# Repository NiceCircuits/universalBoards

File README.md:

# universalBoards
Universal boards for SMD and other. Quick and dirty, 50x50mm - to make in Seeed Studio.

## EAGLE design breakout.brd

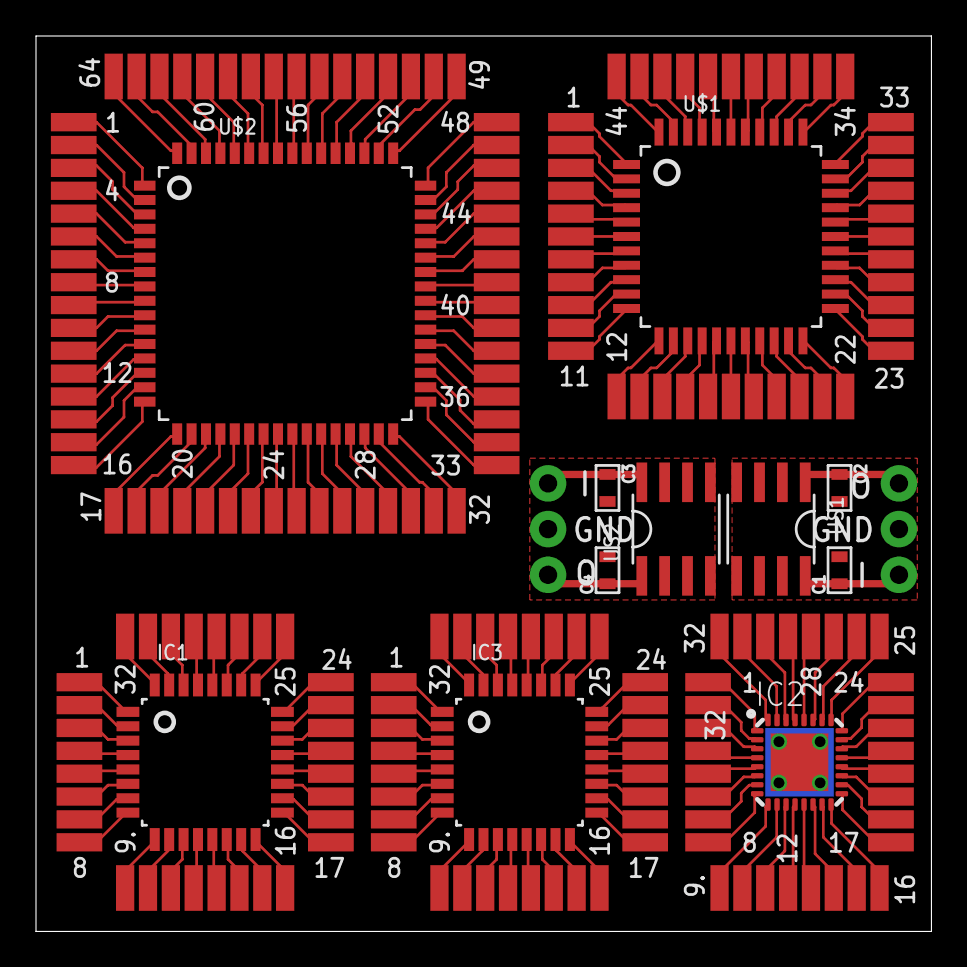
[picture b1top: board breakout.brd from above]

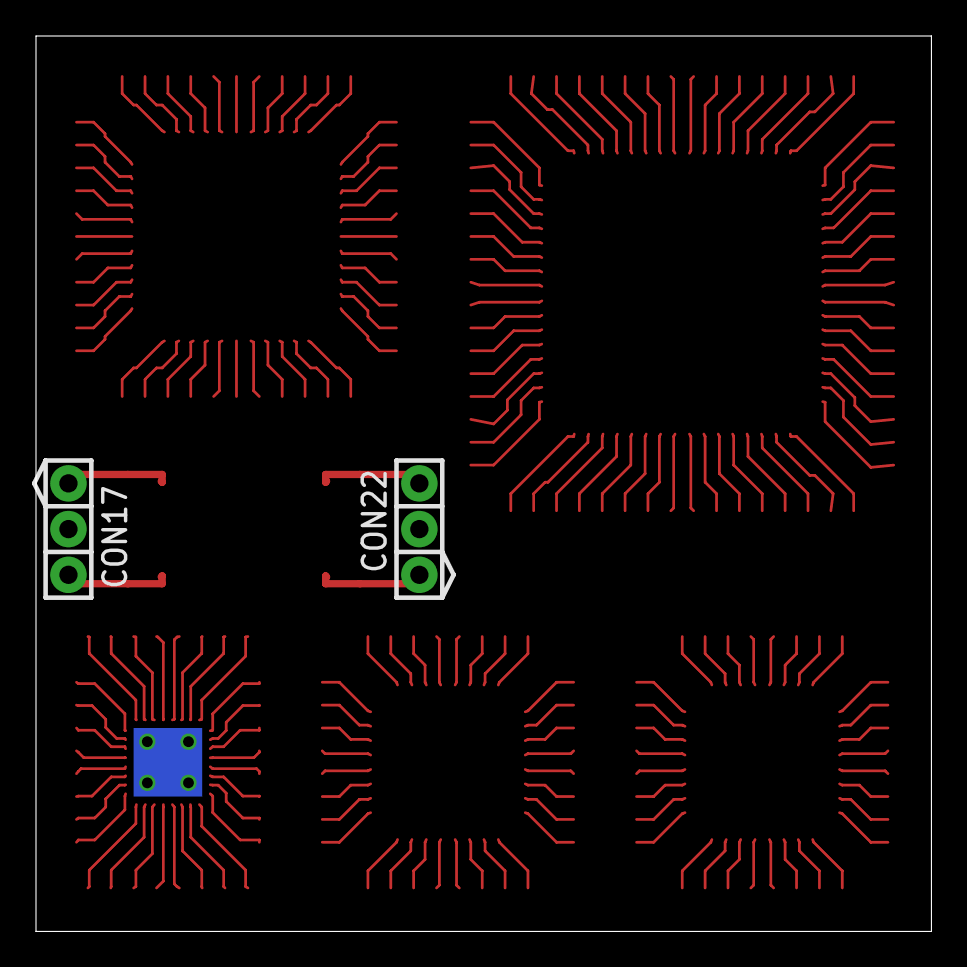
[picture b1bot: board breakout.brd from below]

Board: 2 copper layers, 49.7 x 49.7 mm, 33 parts (2 on the bottom side), 210 nets.

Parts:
C1, C2, C3, C4: 0603
CON1, CON2, CON3, CON4, CON13, CON14, CON15, CON16, CON18, CON19, CON20, CON21: PIN8X1_SM50
CON5, CON6, CON7, CON8: PIN11X1_SM50
CON9, CON10, CON11, CON12: PIN16X1_SM50
CON17, CON22: PIN3X1
IC1, IC3: TQFP32
IC2: MLF32-TH
U$1: 44TQFP; TQFP44
U$2: 64TQFP; TQFP64
US1, US2: SO08

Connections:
unnamed: CON1.P$1, IC1.1
unnamed: CON1.P$2, IC1.2
unnamed: CON1.P$3, IC1.3
unnamed: CON1.P$4, IC1.4
unnamed: CON1.P$5, IC1.5
unnamed: CON1.P$6, IC1.6
unnamed: CON1.P$7, IC1.7
unnamed: CON1.P$8, IC1.8
unnamed: CON2.P$1, IC1.9
unnamed: CON2.P$2, IC1.10
unnamed: CON2.P$3, IC1.11
unnamed: CON2.P$4, IC1.12
unnamed: CON2.P$5, IC1.13
unnamed: CON2.P$6, IC1.14
unnamed: CON2.P$7, IC1.15
unnamed: CON2.P$8, IC1.16
unnamed: CON3.P$1, IC1.17
unnamed: CON3.P$2, IC1.18
unnamed: CON3.P$3, IC1.19
unnamed: CON3.P$4, IC1.20
unnamed: CON3.P$5, IC1.21
unnamed: CON3.P$6, IC1.22
unnamed: CON3.P$7, IC1.23
unnamed: CON3.P$8, IC1.24
unnamed: CON4.P$1, IC1.25
unnamed: CON4.P$2, IC1.26
unnamed: CON4.P$3, IC1.27
unnamed: CON4.P$4, IC1.28
unnamed: CON4.P$5, IC1.29
unnamed: CON4.P$6, IC1.30
unnamed: CON4.P$7, IC1.31
unnamed: CON4.P$8, IC1.32
unnamed: CON5.P$1, U$1.1
unnamed: CON5.P$2, U$1.2
unnamed: CON5.P$3, U$1.3
unnamed: CON5.P$4, U$1.4
unnamed: CON5.P$5, U$1.5
unnamed: CON5.P$6, U$1.6
unnamed: CON5.P$7, U$1.7
unnamed: CON5.P$8, U$1.8
unnamed: CON5.P$9, U$1.9
unnamed: CON5.P$10, U$1.10
unnamed: CON5.P$11, U$1.11
unnamed: CON6.P$1, U$1.12
unnamed: CON6.P$2, U$1.13
unnamed: CON6.P$3, U$1.14
unnamed: CON6.P$4, U$1.15
unnamed: CON6.P$5, U$1.16
unnamed: CON6.P$6, U$1.17
unnamed: CON6.P$7, U$1.18
unnamed: CON6.P$8, U$1.19
unnamed: CON6.P$9, U$1.20
unnamed: CON6.P$10, U$1.21
unnamed: CON6.P$11, U$1.22
unnamed: CON7.P$1, U$1.23
unnamed: CON7.P$2, U$1.24
unnamed: CON7.P$3, U$1.25
unnamed: CON7.P$4, U$1.26
unnamed: CON7.P$5, U$1.27
unnamed: CON7.P$6, U$1.28
unnamed: CON7.P$7, U$1.29
unnamed: CON7.P$8, U$1.30
unnamed: CON7.P$9, U$1.31
unnamed: CON7.P$10, U$1.32
unnamed: CON7.P$11, U$1.33
unnamed: CON8.P$1, U$1.34
unnamed: CON8.P$2, U$1.35
unnamed: CON8.P$3, U$1.36
unnamed: CON8.P$4, U$1.37
unnamed: CON8.P$5, U$1.38
unnamed: CON8.P$6, U$1.39
unnamed: CON8.P$7, U$1.40
unnamed: CON8.P$8, U$1.41
unnamed: CON8.P$9, U$1.42
unnamed: CON8.P$10, U$1.43
unnamed: CON8.P$11, U$1.44
unnamed: CON9.P$1, U$2.1
unnamed: CON9.P$2, U$2.2
unnamed: CON9.P$3, U$2.3
unnamed: CON9.P$4, U$2.4
unnamed: CON9.P$5, U$2.5
unnamed: CON9.P$6, U$2.6
unnamed: CON9.P$7, U$2.7
unnamed: CON9.P$8, U$2.8
unnamed: CON9.P$9, U$2.9
unnamed: CON9.P$10, U$2.10
unnamed: CON9.P$11, U$2.11
unnamed: CON9.P$12, U$2.12
unnamed: CON9.P$13, U$2.13
unnamed: CON9.P$14, U$2.14
unnamed: CON9.P$15, U$2.15
unnamed: CON9.P$16, U$2.16
unnamed: CON10.P$1, U$2.17
unnamed: CON10.P$2, U$2.18
unnamed: CON10.P$3, U$2.19
unnamed: CON10.P$4, U$2.20
unnamed: CON10.P$5, U$2.21
unnamed: CON10.P$6, U$2.22
unnamed: CON10.P$7, U$2.23
unnamed: CON10.P$8, U$2.24
unnamed: CON10.P$9, U$2.25
unnamed: CON10.P$10, U$2.26
unnamed: CON10.P$11, U$2.27
unnamed: CON10.P$12, U$2.28
unnamed: CON10.P$13, U$2.29
unnamed: CON10.P$14, U$2.30
unnamed: CON10.P$15, U$2.31
unnamed: CON10.P$16, U$2.32
unnamed: CON11.P$1, U$2.33
unnamed: CON11.P$2, U$2.34
unnamed: CON11.P$3, U$2.35
unnamed: CON11.P$4, U$2.36
unnamed: CON11.P$5, U$2.37
unnamed: CON11.P$6, U$2.38
unnamed: CON11.P$7, U$2.39
unnamed: CON11.P$8, U$2.40
unnamed: CON11.P$9, U$2.41
unnamed: CON11.P$10, U$2.42
unnamed: CON11.P$11, U$2.43
unnamed: CON11.P$12, U$2.44
unnamed: CON11.P$13, U$2.45
unnamed: CON11.P$14, U$2.46
unnamed: CON11.P$15, U$2.47
unnamed: CON11.P$16, U$2.48
unnamed: CON12.P$1, U$2.49
unnamed: CON12.P$2, U$2.50
unnamed: CON12.P$3, U$2.51
unnamed: CON12.P$4, U$2.52
unnamed: CON12.P$5, U$2.53
unnamed: CON12.P$6, U$2.54
unnamed: CON12.P$7, U$2.55
unnamed: CON12.P$8, U$2.56
unnamed: CON12.P$9, U$2.57
unnamed: CON12.P$10, U$2.58
unnamed: CON12.P$11, U$2.59
unnamed: CON12.P$12, U$2.60
unnamed: CON12.P$13, U$2.61
unnamed: CON12.P$14, U$2.62
unnamed: CON12.P$15, U$2.63
unnamed: CON12.P$16, U$2.64
unnamed: CON13.P$1, IC2.1
unnamed: CON13.P$2, IC2.2
unnamed: CON13.P$3, IC2.3
unnamed: CON13.P$4, IC2.4
unnamed: CON13.P$5, IC2.5
unnamed: CON13.P$6, IC2.6
unnamed: CON13.P$7, IC2.7
unnamed: CON13.P$8, IC2.8
unnamed: CON14.P$1, IC2.9
unnamed: CON14.P$2, IC2.10
unnamed: CON14.P$3, IC2.11
unnamed: CON14.P$4, IC2.12
unnamed: CON14.P$5, IC2.13
unnamed: CON14.P$6, IC2.14
unnamed: CON14.P$7, IC2.15
unnamed: CON14.P$8, IC2.16
unnamed: CON15.P$1, IC2.17
unnamed: CON15.P$2, IC2.18
unnamed: CON15.P$3, IC2.19
unnamed: CON15.P$4, IC2.20
unnamed: CON15.P$5, IC2.21
unnamed: CON15.P$6, IC2.22
unnamed: CON15.P$7, IC2.23
unnamed: CON15.P$8, IC2.24
unnamed: CON16.P$1, IC2.25
unnamed: CON16.P$2, IC2.26
unnamed: CON16.P$3, IC2.27
unnamed: CON16.P$4, IC2.28
unnamed: CON16.P$5, IC2.29
unnamed: CON16.P$6, IC2.30
unnamed: CON16.P$7, IC2.31
unnamed: CON16.P$8, IC2.32
unnamed: C2.1, CON17.1, US1.1
unnamed: C1.1, CON17.3, US1.8
unnamed: C1.2, C2.2, CON17.2, US1.2, US1.3, US1.6, US1.7
unnamed: CON18.P$1, IC3.1
unnamed: CON18.P$2, IC3.2
unnamed: CON18.P$3, IC3.3
unnamed: CON18.P$4, IC3.4
unnamed: CON18.P$5, IC3.5
unnamed: CON18.P$6, IC3.6
unnamed: CON18.P$7, IC3.7
unnamed: CON18.P$8, IC3.8
unnamed: CON19.P$1, IC3.9
unnamed: CON19.P$2, IC3.10
unnamed: CON19.P$3, IC3.11
unnamed: CON19.P$4, IC3.12
unnamed: CON19.P$5, IC3.13
unnamed: CON19.P$6, IC3.14
unnamed: CON19.P$7, IC3.15
unnamed: CON19.P$8, IC3.16
unnamed: CON20.P$1, IC3.17
unnamed: CON20.P$2, IC3.18
unnamed: CON20.P$3, IC3.19
unnamed: CON20.P$4, IC3.20
unnamed: CON20.P$5, IC3.21
unnamed: CON20.P$6, IC3.22
unnamed: CON20.P$7, IC3.23
unnamed: CON20.P$8, IC3.24
unnamed: CON21.P$1, IC3.25
unnamed: CON21.P$2, IC3.26
unnamed: CON21.P$3, IC3.27
unnamed: CON21.P$4, IC3.28
unnamed: CON21.P$5, IC3.29
unnamed: CON21.P$6, IC3.30
unnamed: CON21.P$7, IC3.31
unnamed: CON21.P$8, IC3.32
unnamed: C4.1, CON22.1, US2.1
unnamed: C3.1, CON22.3, US2.8
unnamed: C3.2, C4.2, CON22.2, US2.2, US2.3, US2.6, US2.7

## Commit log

2015-03-22 Readme update
2015-03-22 Routing and gerbers
2015-03-23 Minor corrections. Ready to send.
